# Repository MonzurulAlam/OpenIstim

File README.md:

# <P align="center"> OpenXstim - Open Source Transcutaneous Current Stimulator 
 
### DEVELOPED BY:
Dr Monzurul Alam <br/>
Profile: https://scholar.google.com.au/citations?user=a2yhqEQAAAAJ&hl=en&oi=ao <br/>
Contact: md.malam@connect.polyu.hk <br/>

### OBJECTIVES:
<P align="justify"> The objective of this project is to develop a miniature transcutaneous electrical stimulator for non-invasive muscle and nerve stimulation.

### DESCRIPTION:
<P align="justify"> Transcutaneous electrical spinal cord stimulation, a non-invasive spinal cord neuromodulation method holds tremendous promise and hope to restore functions in people with paralysis resultant of spinal cord injury (SCI), cerebral palsy (CP), stroke and other neurological conditions. Yet, there are not many options of such stimulation devices compared to conventional electrical stimulators such as neuromuscular electrical stimulator (NMES), transcutaneous electrical nerve stimulator (TENS) and functional electrical stimulator (FES), especially for most people with neurological conditions in the developing world.
<P align="justify">  OpenXstim is an open-source programmable electrical stimulator (constant current) is a non-invasive muscle, nerve or spinal cord stimulation device. OpenXstim can generate up to 128 mA current pulses with a compliance voltage up to 96 V per stimulation channel. The stimulator is capable of generating high-frequency (10 kHz) burst stimulation, required for transcutaneous spinal cord stimulation (tSCS).
<P align="justify"> The stimulator contains 5 primary sections: 1) a power management unit build with a few DC-DC converters to serve necessary power for the stimulator, 2) a Microcontroller unit for easy programming that provides necessary parameters for the stimulation, 3) a control and display unit to vary the stimulation parameters and display the values, 4) a Digital-to-Analog Converter (DAC) to generate voltage stimulation pulses, 5) a Voltage-to-Current converter unit to convert voltage pulses into appropriate current pulse.

### DISCLAIMER:
<P align="justify"> The design is offered as it is. Although it has been regorously tested with utmost care and to the best of my knowledge, I do not provide any warranty in any aspect.

### WARNING:
- The design is intended stricktly for research and education purposes.
- The stimulator is not approved for human or animal and cannot be used without receving prior approval from appropriate ethics committee such as Institutional Review Board.
- The stimulator can generate high voltage and under no circumstances it should be placed across the chest or close to the heart.
- The stimulator should never be powered from external adapter, USB or power source while being used or connected to the body.

### LICENSE:
##### Documentation licensed under the Creative Commons Attribution Share Alike (CC BY-SA) 4.0 International License

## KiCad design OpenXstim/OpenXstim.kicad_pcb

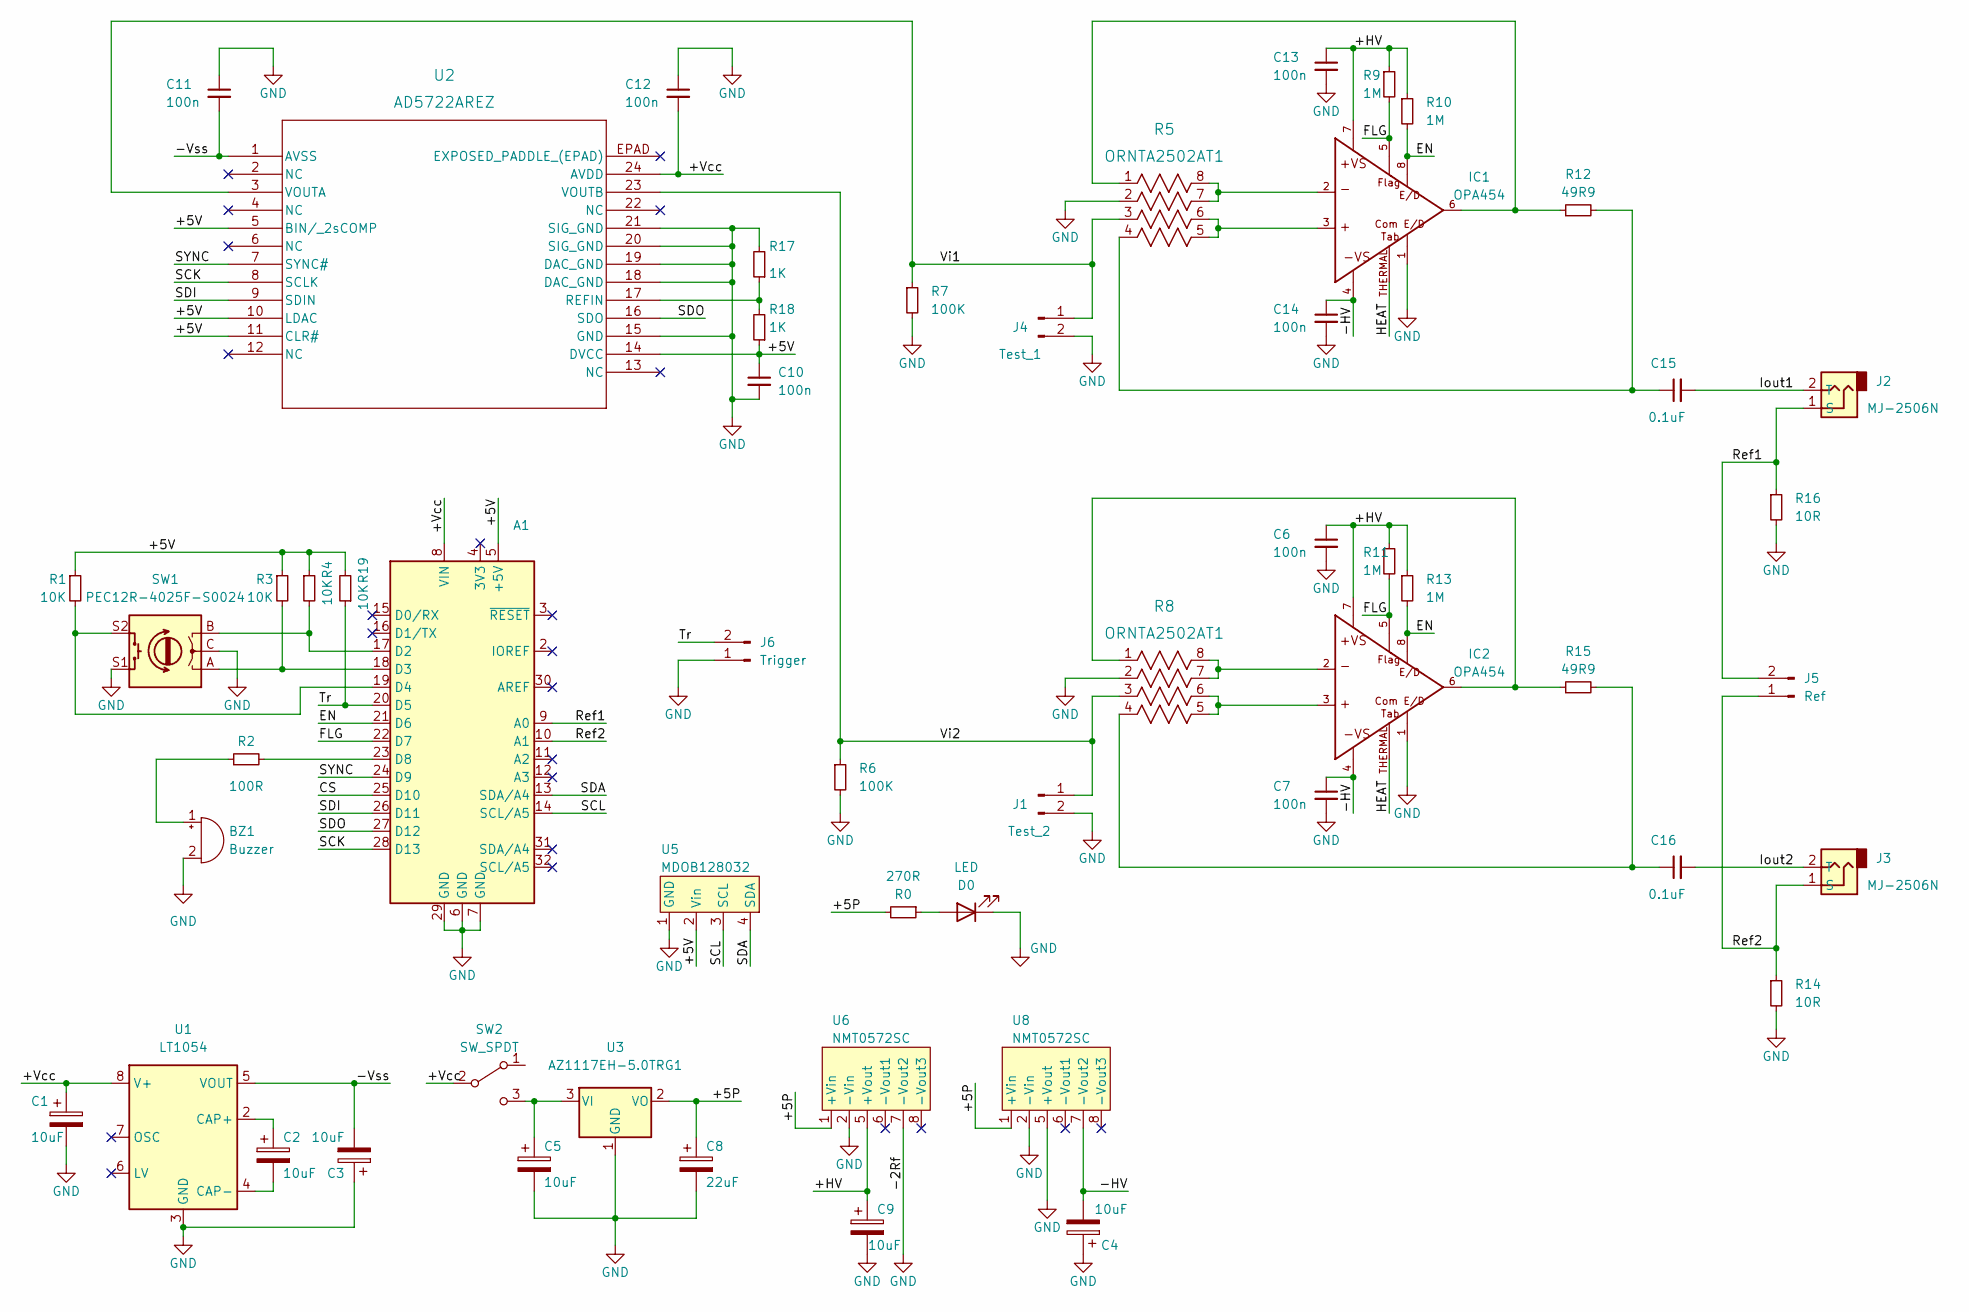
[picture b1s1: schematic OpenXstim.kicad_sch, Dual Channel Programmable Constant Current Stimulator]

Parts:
A1: (no value)
BZ1: Buzzer; Buzzer_12x9.5RM7.6
C1, C5: 10uF; C_1206_3216Metric
C2, C3: 10uF; CP_Elec_5x5.3
C4, C9: 10uF; CP_Elec_8x10.5
C6, C7, C10, C11, C12, C13, C14: 100n; C_0805_2012Metric
C8: 22uF; CP_Elec_5x5.4
C15, C16: 0.1uF; C_0805_2012Metric
D0: LED; LED_1206_3216Metric
IC1, IC2: OPA454; SO08GP; PARTNUM 296-22997-5-ND
J1: Test_2; PinHeader_1x02_P2.54mm_Vertical
J2, J3: MJ-2506N; CUI_MJ-2506N
J4: Test_1; PinHeader_1x02_P2.54mm_Vertical
J5: Ref; PinHeader_1x02_P2.54mm_Vertical
J6: Trigger; PinHeader_1x02_P2.54mm_Vertical
R0: 270R; R_0805_2012Metric
R1, R3, R4, R19: 10K; R_0805_2012Metric
R2: 100R; R_0805_2012Metric
R5, R8: ORNTA2502AT1; ORN_VIS
R6, R7: 100K; R_0805_2012Metric
R9, R10, R11, R13: 1M; R_0805_2012Metric
R12, R15: 49R9; R_0805_2012Metric
R14, R16: 10R; R_0805_2012Metric
R17, R18: 1K; R_0805_2012Metric
SW1: PEC12R-4025F-S0024; ENC_PEC12R-4025F-S0024
SW2: SW_SPDT; SW_MINI-SPDT-SW
U1: LT1054; SOIC-8_3.9x4.9mm_P1.27mm
U2: AD5722AREZ; RE_24_ADI
U3: AZ1117EH-5.0TRG1; SOT-223
U5: MDOB128032; MDOB128032GV-WI
U6, U8: NMT0572SC

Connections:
/+5P: C8.1, R0.2, U3.2 (VO), U6.1 (+Vin), U8.1 (+Vin)
/+5V: A1.5 (+5V), C10.1, R1.1, R3.1, R4.1, R18.1, R19.2, U2.5 (BIN/_2sCOMP), U2.10 (LDAC), U2.11 (CLR#), U2.14 (DVCC), U5.2 (Vin)
/+HV: C6.1, C9.1, C13.1, IC1.7, IC2.7, R9.1, R10.1, R11.1, R13.1, U6.5 (+Vout)
/+Vcc: A1.8 (VIN), C1.1, C12.2, SW2.2 (B), U1.8 (V+), U2.24 (AVDD)
/-HV: C4.2, C7.1, C14.1, IC1.4, IC2.4, U8.7 (-Vout2)
/-Vss: C3.2, C11.2, U1.5 (VOUT), U2.1 (AVSS)
/CS: A1.25 (D10)
/EN: A1.21 (D6), IC1.8, IC2.8, R10.2, R13.2
/FLG: A1.22 (D7), IC1.5, IC2.5, R9.2, R11.2
/HEAT: IC1.THERMAL, IC2.THERMAL
/Iout1: C15.2, J2.2 (T)
/Iout2: C16.2, J3.2 (T)
/Ref1: A1.9 (A0), J2.1 (S), J5.2, R16.1
/Ref2: A1.10 (A1), J3.1 (S), J5.1, R14.1
/SCK: A1.28 (D13), U2.8 (SCLK)
/SCL: A1.14 (SCL/A5), U5.3 (SCL)
/SDA: A1.13 (SDA/A4), U5.4 (SDA)
/SDI: A1.26 (D11), U2.9 (SDIN)
/SDO: A1.27 (D12), U2.16 (SDO)
/SYNC: A1.24 (D9), U2.7 (SYNC#)
/Tr: A1.20 (D5), J6.2, R19.1
/Vi1: J4.1, R5.3, R7.1, U2.3 (VOUTA)
/Vi2: J1.1, R6.1, R8.3, U2.23 (VOUTB)
GND: A1.6 (GND), A1.7 (GND), A1.29 (GND), BZ1.2 (+), C1.2, C3.1, C4.1, C5.2, C6.2, C7.2, C8.2, C9.2, C10.2, C11.1, C12.1, C13.2, C14.2, D0.1 (K), IC1.1, IC2.1, J1.2, J4.2, J6.1, R5.2, R6.2, R7.2, R8.2, R14.2, R16.2, R17.2, SW1.C, SW1.S1, U1.3 (GND), U2.15 (GND), U2.18 (DAC_GND), U2.19 (DAC_GND), U2.20 (SIG_GND), U2.21 (SIG_GND), U3.1 (GND), U5.1 (GND), U6.2 (-Vin), U6.7 (-Vout2), U8.2 (-Vin), U8.5 (+Vout)
unnamed: A1.17 (D2), R4.2, SW1.B
unnamed: A1.18 (D3), R3.2, SW1.A
unnamed: A1.19 (D4), R1.2, SW1.S2
unnamed: A1.23 (D8), R2.2
unnamed: BZ1.1 (-), R2.1
unnamed: C2.1, U1.2 (CAP+)
unnamed: C2.2, U1.4 (CAP-)
unnamed: C5.1, SW2.3 (C), U3.3 (VI)
unnamed: C15.1, R5.4, R12.2
unnamed: C16.1, R8.4, R15.2
unnamed: D0.2 (A), R0.1
unnamed: IC1.2, R5.7, R5.8
unnamed: IC1.3, R5.5, R5.6
unnamed: IC1.6, R5.1, R12.1
unnamed: IC2.2, R8.7, R8.8
unnamed: IC2.3, R8.5, R8.6
unnamed: IC2.6, R8.1, R15.1
unnamed: R17.1, R18.2, U2.17 (REFIN)

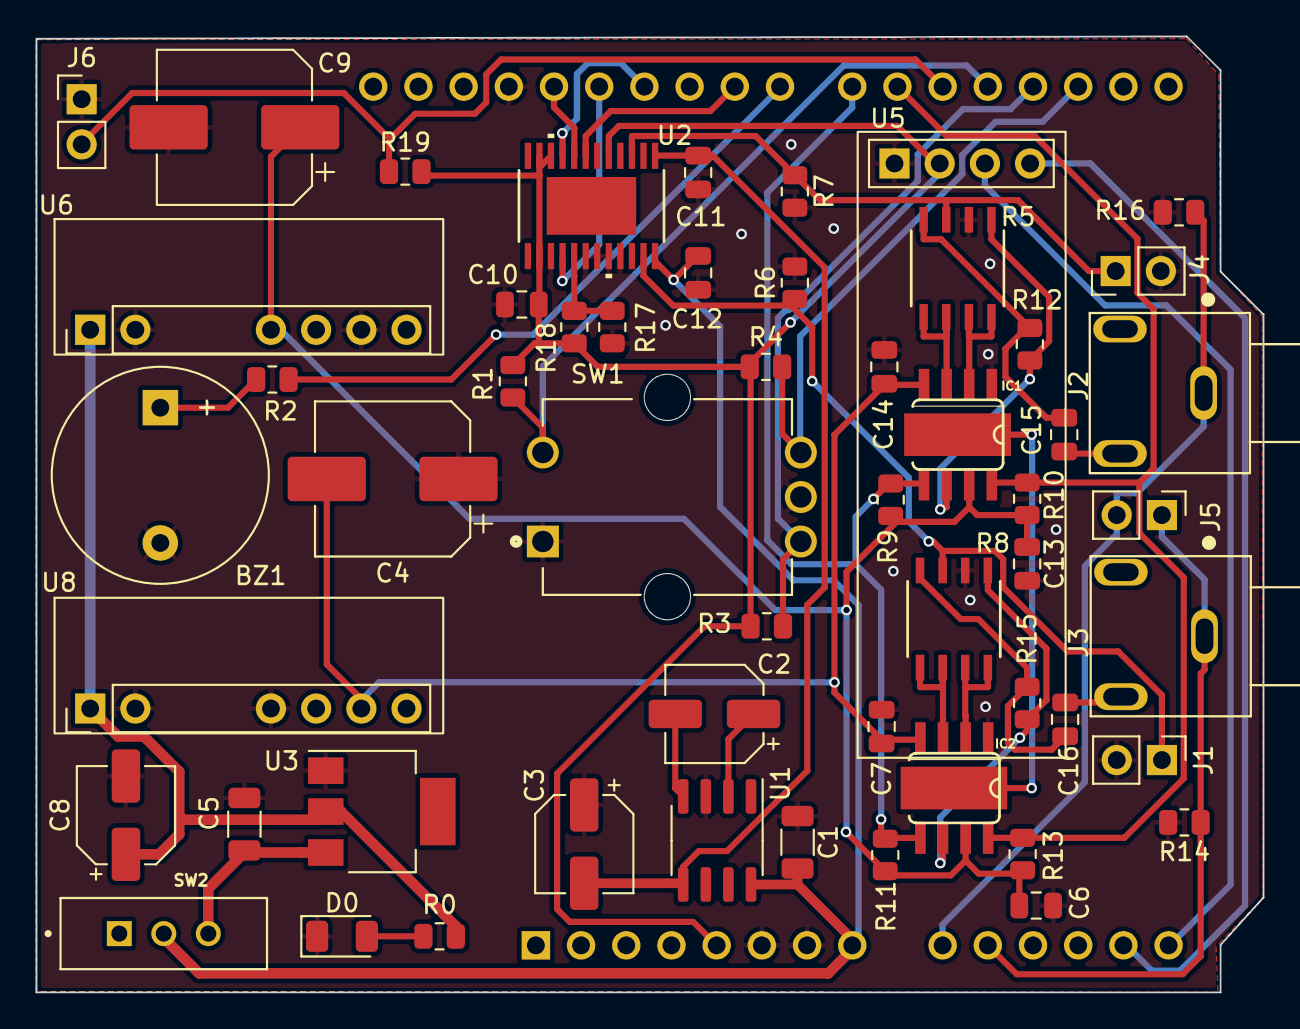
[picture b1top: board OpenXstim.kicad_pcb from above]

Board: 2 copper layers, 69.0 x 53.7 mm, 55 parts (1 on the bottom side), 41 nets.

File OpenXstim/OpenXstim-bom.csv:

Comment,Designator,Footprint
Buzzer,BZ1,Buzzer_Beeper:Buzzer_12x9.5RM7.6
10uF,"C2, C3",Capacitor_SMD:CP_Elec_5x5.3
10uF,"C1, C5",Capacitor_SMD:C_1206_3216Metric
22uF,C8,Capacitor_SMD:CP_Elec_5x5.4
10uF,"C4, C9",Capacitor_SMD:CP_Elec_8x10.5
100n,"C6, C7, C10, C11, C12, C13, C14",Capacitor_SMD:C_0805_2012Metric
0.1uF,"C15, C16",Capacitor_SMD:C_0805_2012Metric
LED,D0,LED_SMD:LED_1206_3216Metric
OPA454,"IC1, IC2",RehabExo:SO08GP
Test_2,J1,Connector_PinHeader_2.54mm:PinHeader_1x02_P2.54mm_Vertical
MJ-2506N,"J2, J3",RehabExo:CUI_MJ-2506N
Test_1,J4,Connector_PinHeader_2.54mm:PinHeader_1x02_P2.54mm_Vertical
Ref,J5,Connector_PinHeader_2.54mm:PinHeader_1x02_P2.54mm_Vertical
Trigger,J6,Connector_PinHeader_2.54mm:PinHeader_1x02_P2.54mm_Vertical
270R,R0,Resistor_SMD:R_0805_2012Metric
100R,R2,Resistor_SMD:R_0805_2012Metric
10K,"R1, R3, R4, R19",Resistor_SMD:R_0805_2012Metric
ORNTA2502AT1,"R5, R8",RehabExo:ORN_VIS
100K,"R6, R7",Resistor_SMD:R_0805_2012Metric
1M,"R9, R10, R11, R13",Resistor_SMD:R_0805_2012Metric
49R9,"R12, R15",Resistor_SMD:R_0805_2012Metric
10R,"R14, R16",Resistor_SMD:R_0805_2012Metric
1K,"R17, R18",Resistor_SMD:R_0805_2012Metric
PEC12R-4025F-S0024,SW1,RehabExo:ENC_PEC12R-4025F-S0024
SW_SPDT,SW2,RehabExo:SW_MINI-SPDT-SW
LT1054,U1,Package_SO:SOIC-8_3.9x4.9mm_P1.27mm
AD5722AREZ,U2,RehabExo:RE_24_ADI
AZ1117EH-5.0TRG1,U3,Package_TO_SOT_SMD:SOT-223
MDOB128032,U5,RehabExo:MDOB128032GV-WI
NMT0572SC,"U6, U8",RehabExo:NMT0572SC

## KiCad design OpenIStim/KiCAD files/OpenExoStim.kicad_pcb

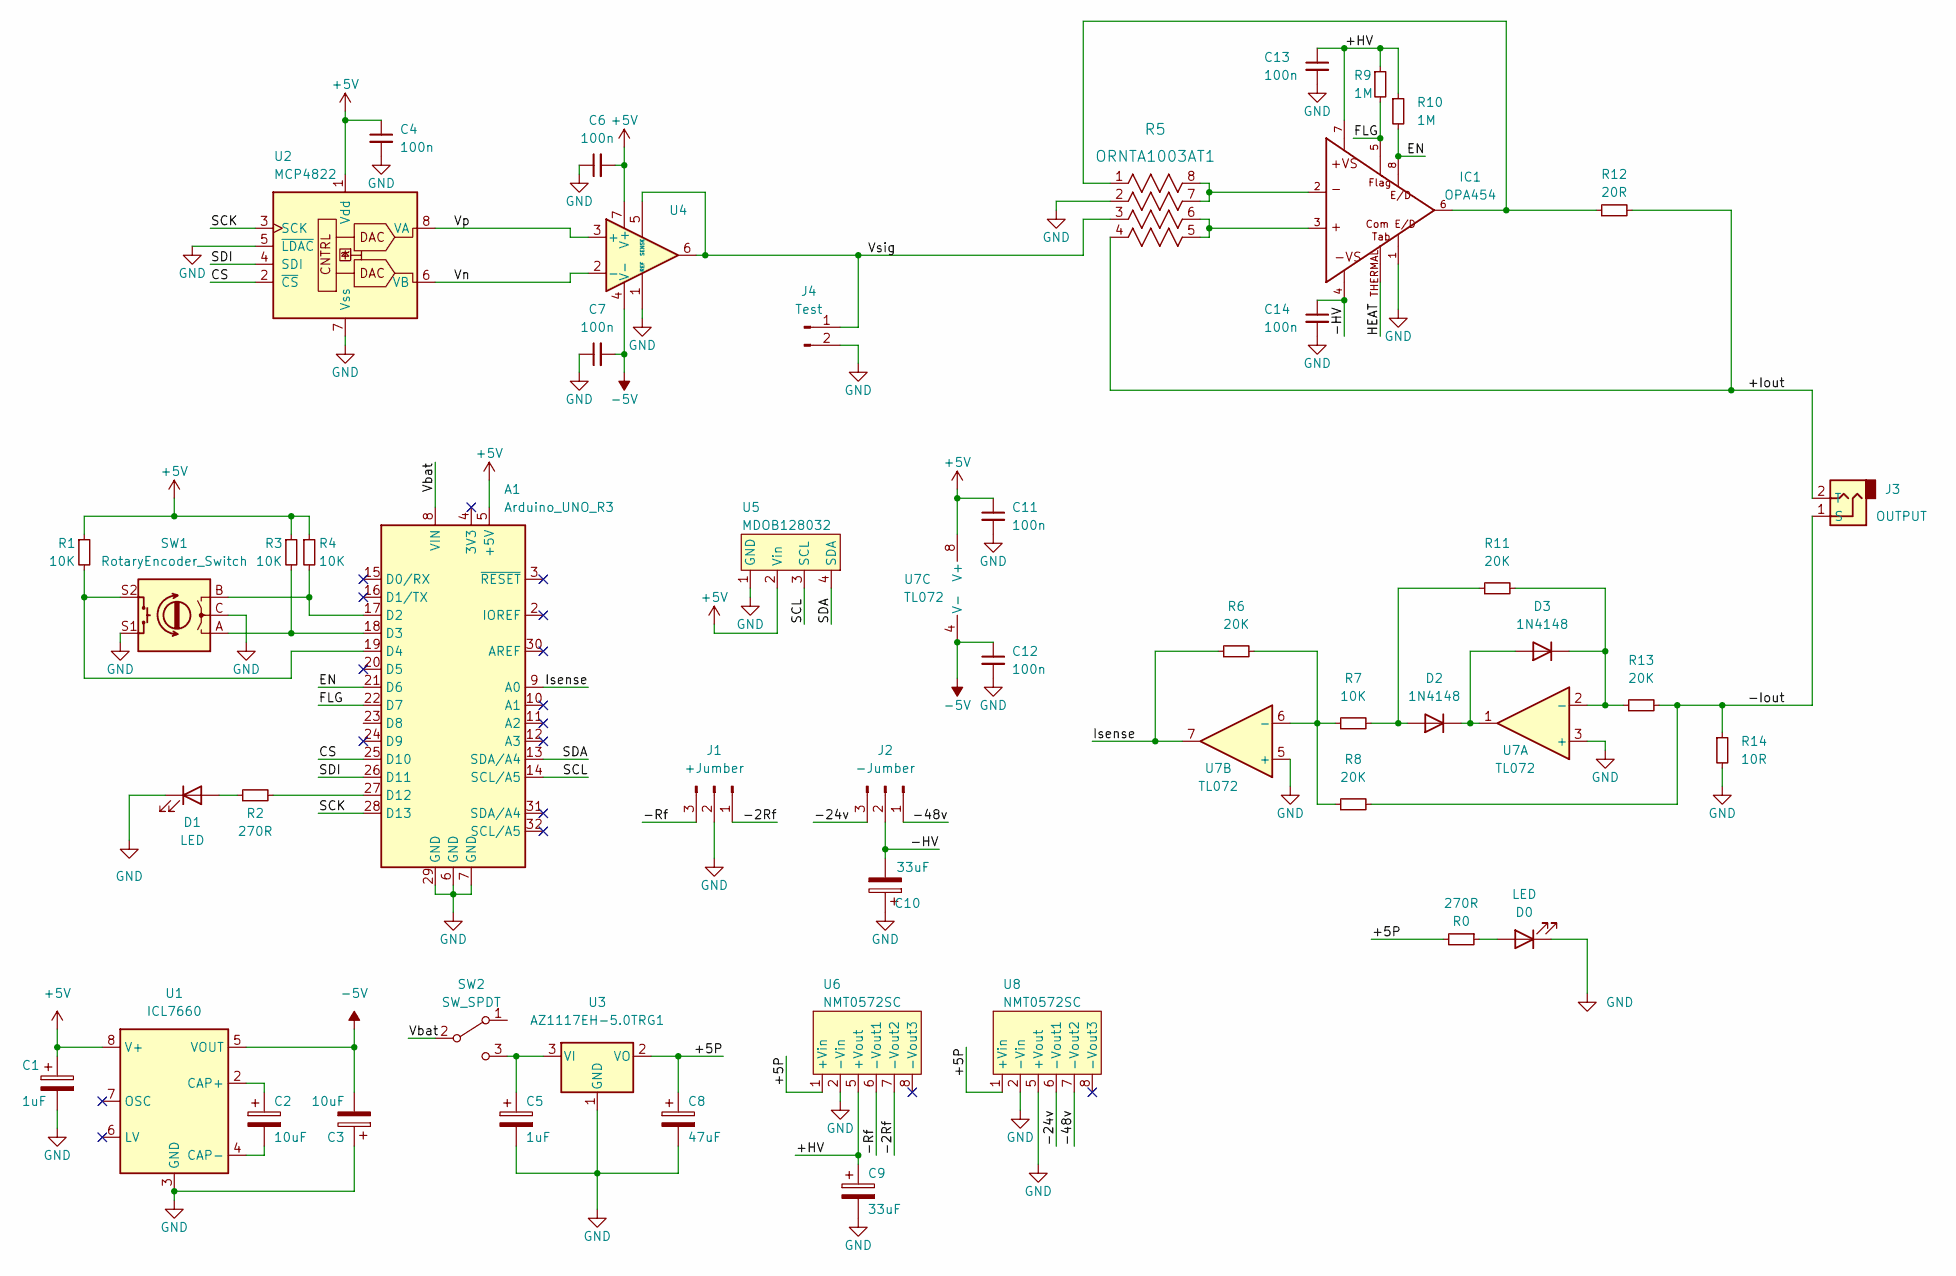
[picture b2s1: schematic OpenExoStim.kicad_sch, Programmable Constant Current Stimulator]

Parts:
A1: Arduino_UNO_R3
C1, C5: 1uF; C_1206_3216Metric
C2, C3: 10uF; CP_Elec_5x5.3
C4, C6, C7, C11, C12, C13, C14: 100n; C_0805_2012Metric
C8: 47uF; CP_Elec_5x5.4
C9, C10: 33uF; CP_Elec_8x10.5
D0, D1: LED; LED_1206_3216Metric
D2, D3: 1N4148; D_SOD-123
IC1: OPA454; SO08GP; PARTNUM 296-22997-5-ND
J1: +Jumber; PinHeader_1x03_P2.54mm_Vertical
J2: -Jumber; PinHeader_1x03_P2.54mm_Vertical
J3: OUTPUT; CUI_MJ-2506N
J4: Test; PinHeader_1x02_P2.54mm_Vertical
R0, R2: 270R; R_0805_2012Metric
R1, R3, R4, R7: 10K; R_0805_2012Metric
R5: ORNTA1003AT1; ORN_VIS
R6, R8, R11, R13: 20K; R_0805_2012Metric
R9, R10: 1M; R_0805_2012Metric
R12: 20R; R_Axial_DIN0207_L6.3mm_D2.5mm_P10.16mm_Horizontal
R14: 10R; R_Axial_DIN0207_L6.3mm_D2.5mm_P10.16mm_Horizontal
SW1: RotaryEncoder_Switch; ENC_PEC12R-4025F-S0024
SW2: SW_SPDT; SW_MINI-SPDT-SW
U1: ICL7660; SOIC-8_3.9x4.9mm_P1.27mm
U2: MCP4822; SOIC-8_3.9x4.9mm_P1.27mm
U3: AZ1117EH-5.0TRG1; SOT-223
U4: SOIC-8_3.9x4.9mm_P1.27mm
U5: MDOB128032; MDOB128032GV-WI
U6, U8: NMT0572SC
U7: TL072; SOIC-8_3.9x4.9mm_P1.27mm

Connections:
+5V: A1.5 (+5V), C1.1, C4.1, C6.2, C11.1, R1.1, R3.1, R4.1, U1.8 (V+), U2.1 (Vdd), U4.7 (V+), U5.2 (Vin), U7.8 (V+)
-5V: C3.2, C7.2, C12.1, U1.5 (VOUT), U4.4 (V-), U7.4 (V-)
/+5P: C8.1, R0.2, U3.2 (VO), U6.1 (+Vin), U8.1 (+Vin)
/+HV: C9.1, C13.1, IC1.7, R9.1, R10.1, U6.5 (+Vout)
/+Iout: J3.2 (T), R5.4, R12.2
/-2Rf: J1.1, U6.7 (-Vout2)
/-24v: J2.3, U8.6 (-Vout1)
/-48v: J2.1, U8.7 (-Vout2)
/-HV: C10.2, C14.1, IC1.4, J2.2
/-Iout: J3.1 (S), R8.2, R13.2, R14.1
/-Rf: J1.3, U6.6 (-Vout1)
/CS: A1.25 (D10), U2.2 (~CS)
/EN: A1.21 (D6), IC1.8, R10.2
/FLG: A1.22 (D7), IC1.5, R9.2
/HEAT: IC1.THERMAL
/Isense: A1.9 (A0), R6.1, U7.7
/SCK: A1.28 (D13), U2.3 (SCK)
/SCL: A1.14 (SCL/A5), U5.3 (SCL)
/SDA: A1.13 (SDA/A4), U5.4 (SDA)
/SDI: A1.26 (D11), U2.4 (SDI)
/Vbat: A1.8 (VIN), SW2.2 (B)
/Vn: U2.6 (VB), U4.2 (-)
/Vp: U2.8 (VA), U4.3 (+)
/Vsig: J4.1, R5.3, U4.5 (SENSE), U4.6
GND: A1.6 (GND), A1.7 (GND), A1.29 (GND), C1.2, C3.1, C4.2, C5.2, C6.1, C7.1, C8.2, C9.2, C10.1, C11.2, C12.2, C13.2, C14.2, D0.1 (K), D1.1 (K), IC1.1, J1.2, J4.2, R5.2, R14.2, SW1.C, SW1.S1, U1.3 (GND), U2.5 (~LDAC), U2.7 (Vss), U3.1 (GND), U4.1 (REF), U5.1 (GND), U6.2 (-Vin), U7.3 (+), U7.5 (+), U8.2 (-Vin), U8.5 (+Vout)
unnamed: A1.17 (D2), R4.2, SW1.B
unnamed: A1.18 (D3), R3.2, SW1.A
unnamed: A1.19 (D4), R1.2, SW1.S2
unnamed: A1.27 (D12), R2.2
unnamed: C2.1, U1.2 (CAP+)
unnamed: C2.2, U1.4 (CAP-)
unnamed: C5.1, SW2.3 (C), U3.3 (VI)
unnamed: D0.2 (A), R0.1
unnamed: D1.2 (A), R2.1
unnamed: D2.1 (K), D3.2 (A), U7.1
unnamed: D2.2 (A), R7.2, R11.1
unnamed: D3.1 (K), R11.2, R13.1, U7.2 (-)
unnamed: IC1.2, R5.7, R5.8
unnamed: IC1.3, R5.5, R5.6
unnamed: IC1.6, R5.1, R12.1
unnamed: R6.2, R7.1, R8.1, U7.6 (-)

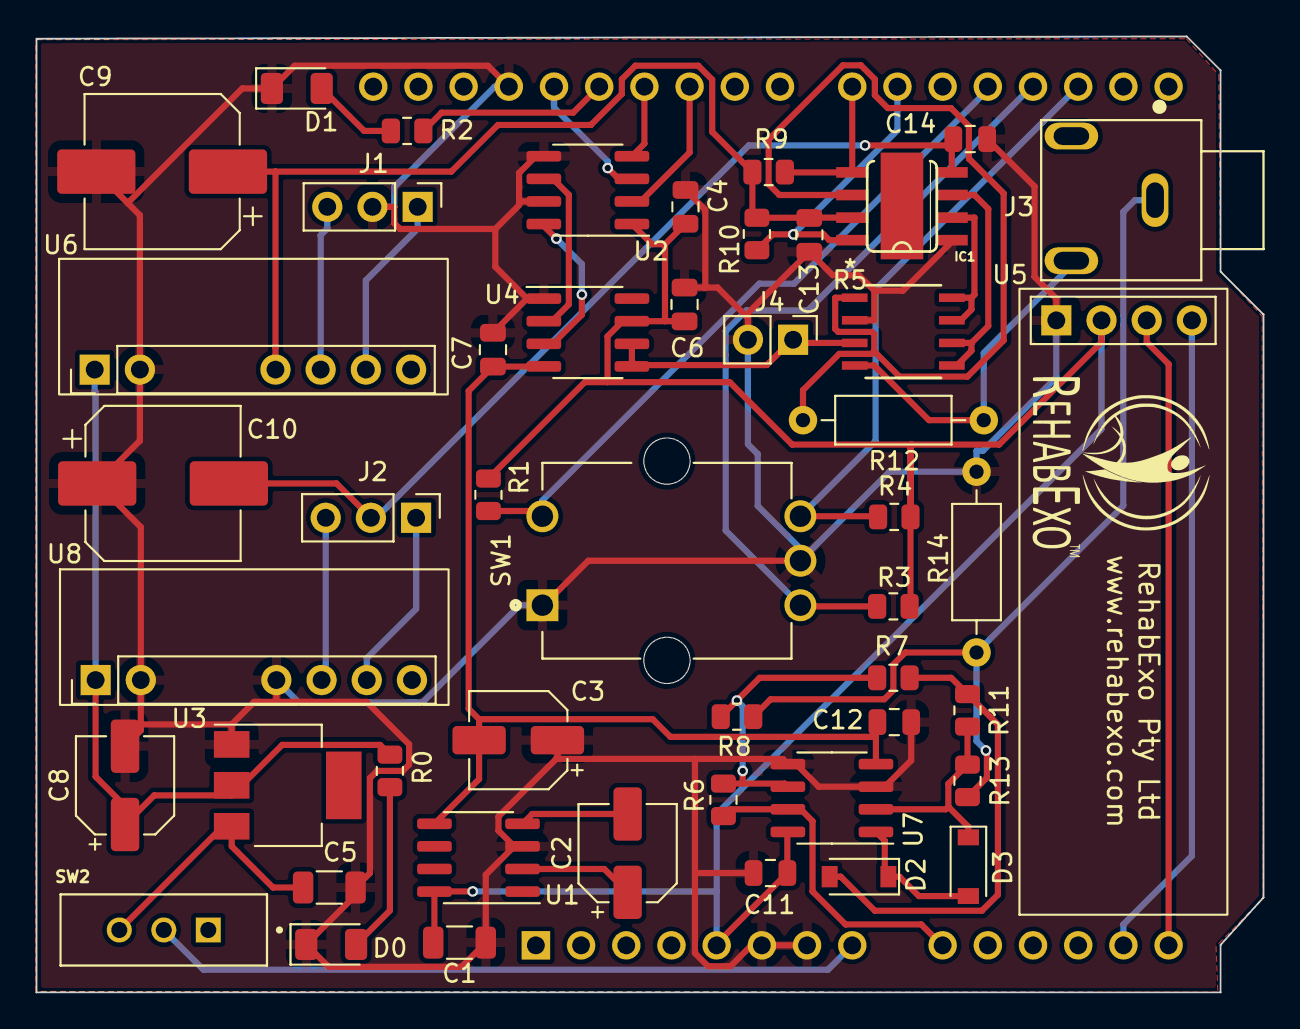
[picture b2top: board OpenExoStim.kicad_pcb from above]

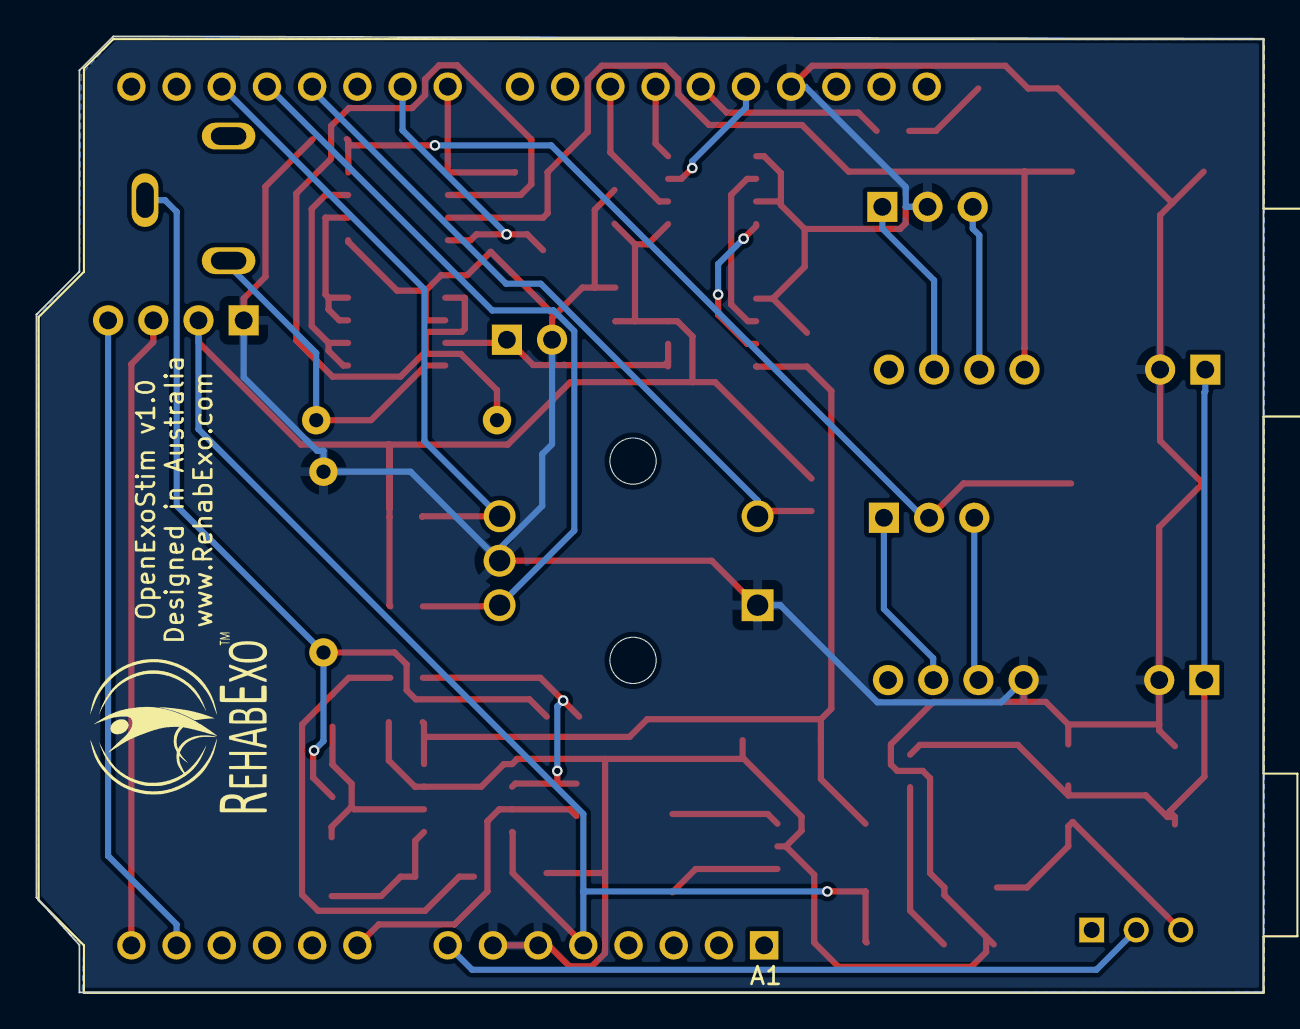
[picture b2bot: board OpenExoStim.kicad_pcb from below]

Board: 2 copper layers, 69.0 x 53.7 mm, 51 parts (2 on the bottom side), 40 nets.

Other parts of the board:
G1, G2: LOGO; RehabExoNameLogo_11mmx15.6mm

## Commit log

2023-10-21 Rename OpenIStim/OpenXstim_Schematics.pdf
